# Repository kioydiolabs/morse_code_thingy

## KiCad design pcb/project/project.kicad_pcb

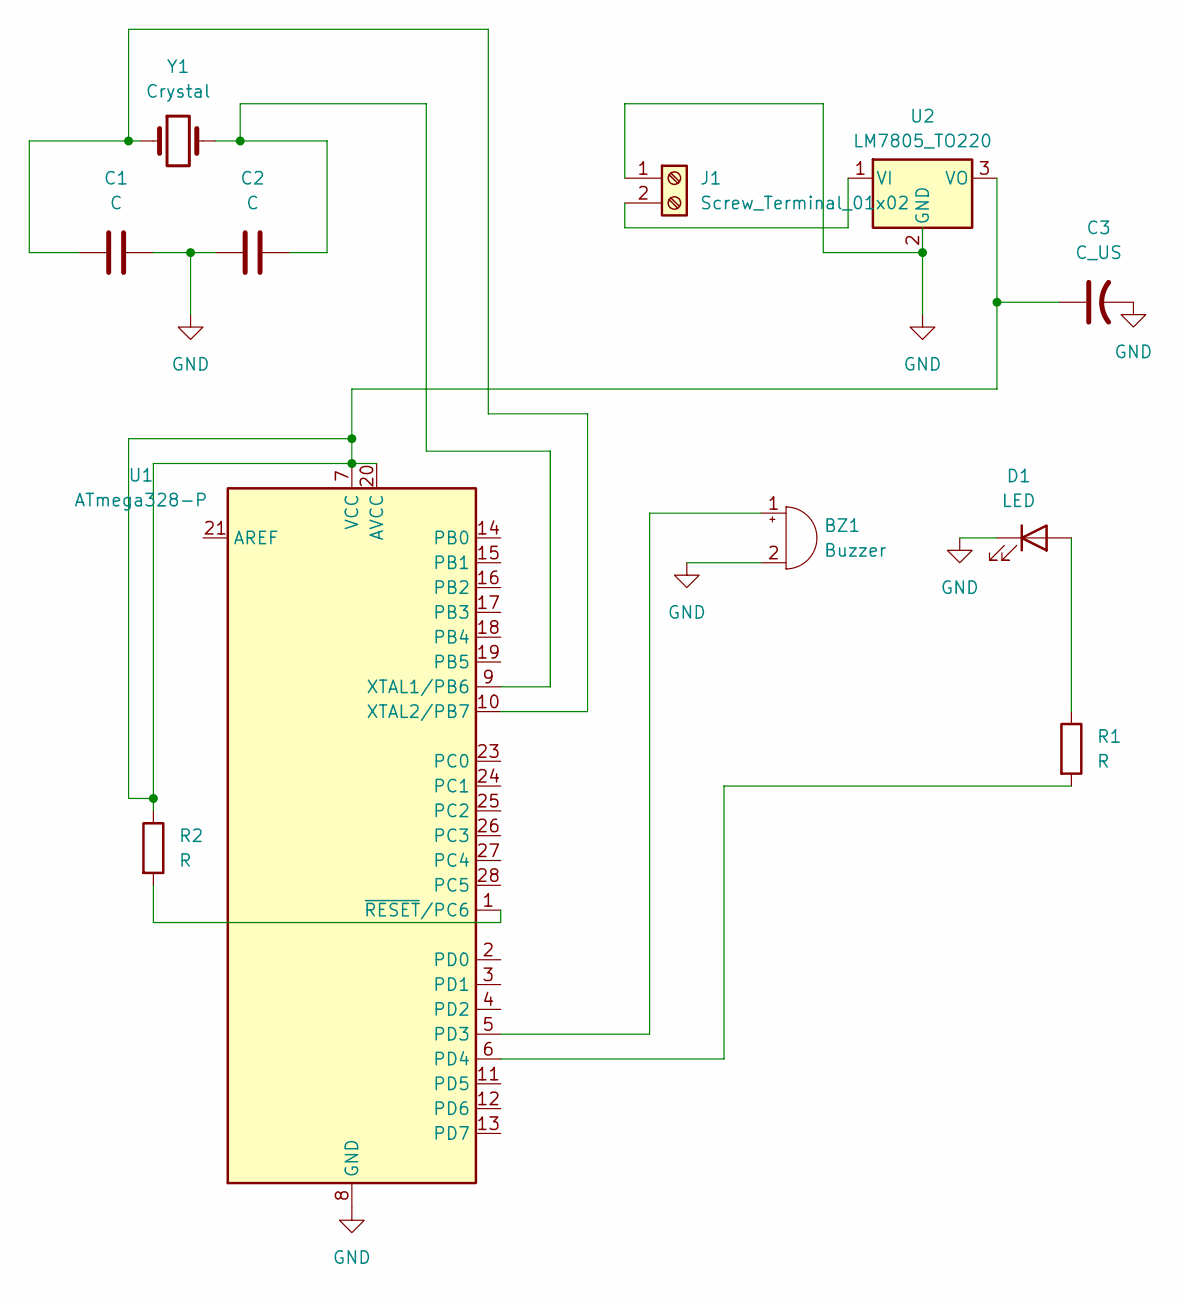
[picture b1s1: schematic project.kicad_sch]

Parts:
BZ1: Buzzer; Buzzer_12x9.5RM7.6
C1, C2: C; C_Disc_D3.0mm_W1.6mm_P2.50mm
C3: C_US; C_Radial_D5.0mm_H11.0mm_P2.00mm
D1: LED; LED_D5.0mm_Clear
J1: Screw_Terminal_01x02; TerminalBlock_MaiXu_MX126-5.0-02P_1x02_P5.00mm
R1, R2: R; R_Axial_DIN0207_L6.3mm_D2.5mm_P7.62mm_Horizontal
U1: ATmega328-P; DIP-28_W7.62mm_Socket
U2: LM7805_TO220; TO-220-3_Vertical
Y1: Crystal; Crystal_HC50_Vertical

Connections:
GND: BZ1.2 (-), C1.1, C2.2, C3.2, D1.1 (K), J1.1, U1.8 (GND), U1.22 (GND), U2.2 (GND)
unnamed: BZ1.1 (+), U1.5 (PD3)
unnamed: D1.2 (A), R1.1
unnamed: J1.2, U2.1 (VI)
unnamed: C3.1, R2.1, U1.7 (VCC), U1.20 (AVCC), U2.3 (VO)
unnamed: R1.2, U1.6 (PD4)
unnamed: C2.1, U1.9 (XTAL1/PB6), Y1.2
unnamed: C1.2, U1.10 (XTAL2/PB7), Y1.1
unnamed: R2.2, U1.1 (~RESET/PC6)

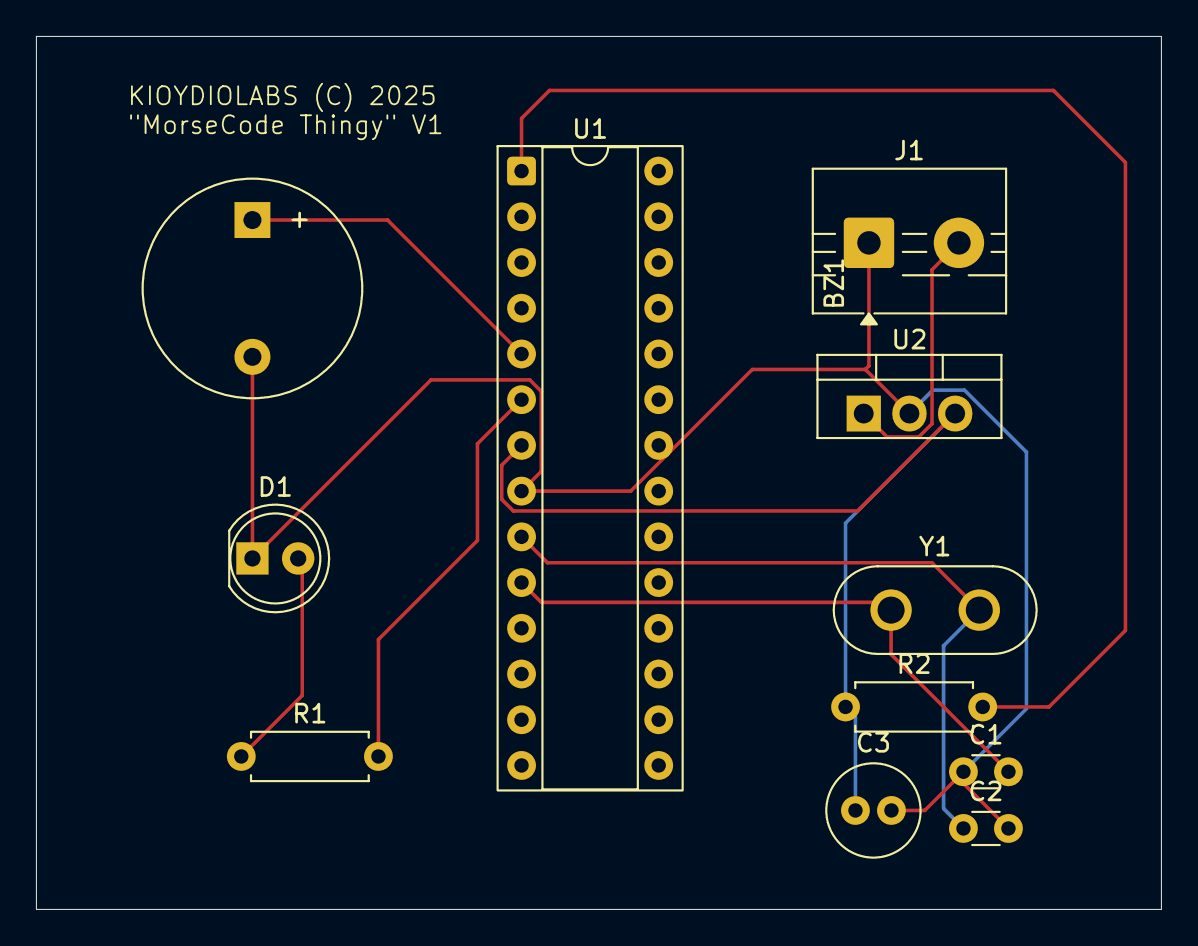
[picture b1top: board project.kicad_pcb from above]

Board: 2 copper layers, 62.5 x 48.5 mm, 11 parts (0 on the bottom side), 9 nets.

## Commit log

2025-07-02 init
2025-07-02 change to arduino functions
2025-07-02 separate config into different file (config.h)
2025-07-02 fix schematic a bit
2025-07-02 add a couple of kicad files to gitignore

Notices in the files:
pcb/project/project.kicad_pcb:
KIOYDIOLABS (C) 2025
